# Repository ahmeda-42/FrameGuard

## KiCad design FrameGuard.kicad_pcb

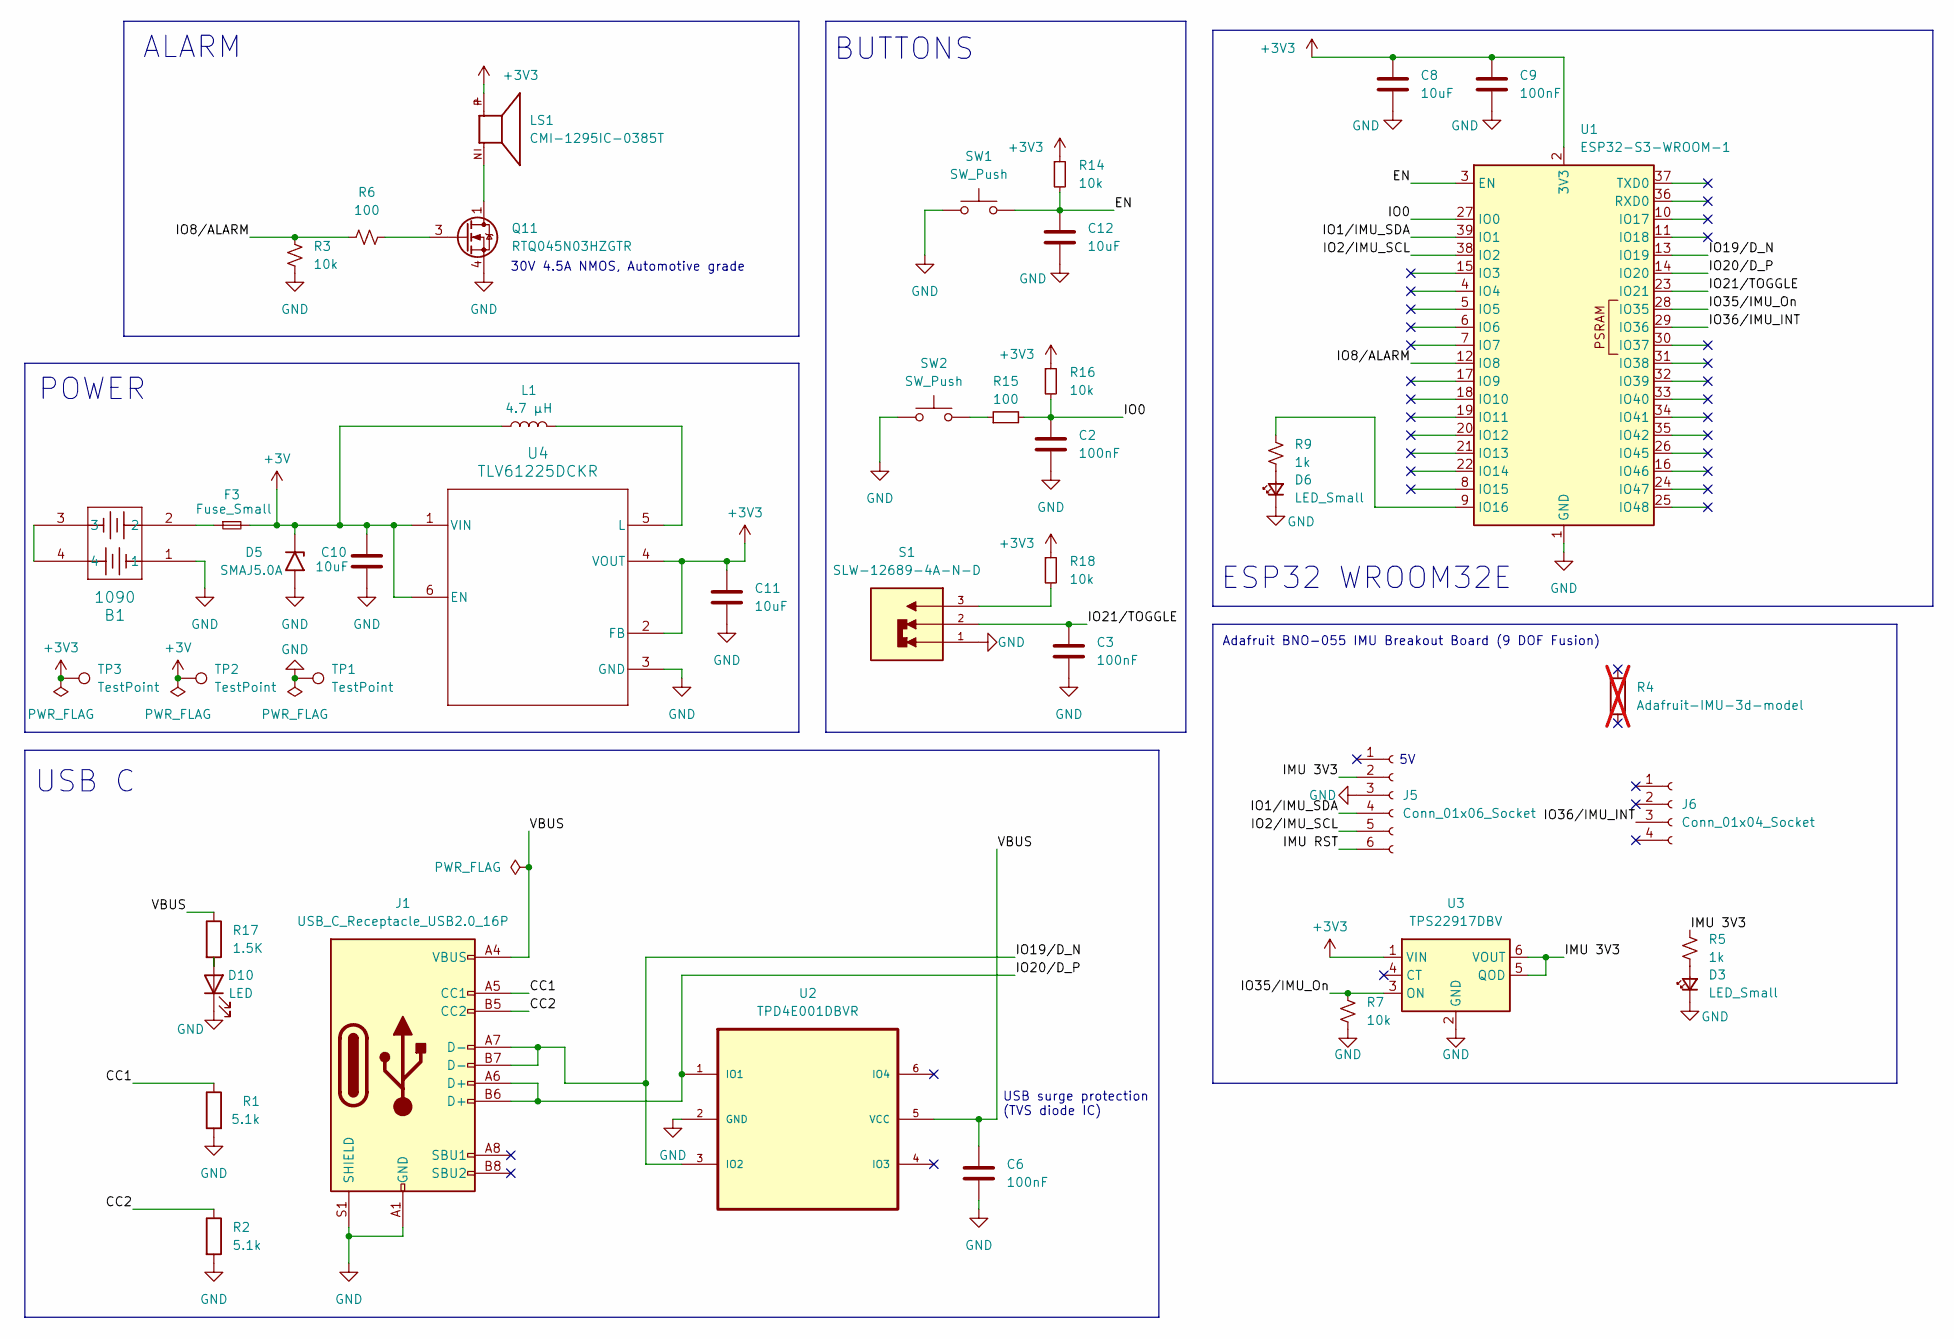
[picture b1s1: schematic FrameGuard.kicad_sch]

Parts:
B1: 1090; BATTERY-1090_KEY
C2, C3, C6, C9: 100nF; C_0603_1608Metric_Pad1.08x0.95mm_HandSolder
C8, C10, C11, C12: 10uF; C_0603_1608Metric_Pad1.08x0.95mm_HandSolder
D3, D6: LED_Small; LED_0805_2012Metric_Pad1.15x1.40mm_HandSolder
D5: SMAJ5.0A; D_SMA_Handsoldering
D10: LED; LED_0603_1608Metric_Pad1.05x0.95mm_HandSolder
F3: Fuse_Small; Fuse_1812_4532Metric_Pad1.30x3.40mm_HandSolder
J1: USB_C_Receptacle_USB2.0_16P; USB_C_Receptacle_GCT_USB4085
J5: Conn_01x06_Socket; PinSocket_1x06_P2.54mm_Vertical
J6: Conn_01x04_Socket; PinSocket_1x04_P2.54mm_Vertical
L1: 4.7 µH; L_0805_2012Metric_Pad1.05x1.20mm_HandSolder
LS1: CMI-1295IC-0385T; BUZZER-CUI_CMI-1295IC-0385T; PARTREV 1.0
Q11: RTQ045N03HZGTR; TSOT-23-6_HandSoldering
R1, R2: 5.1k; R_0603_1608Metric_Pad0.98x0.95mm_HandSolder
R3: 10k; R_0603_1608Metric_Pad0.98x0.95mm_HandSolder
R4: Adafruit-IMU-3d-model; R_0603_1608Metric_Pad0.98x0.95mm_HandSolder; not fitted
R5, R9: 1k; R_0805_2012Metric_Pad1.20x1.40mm_HandSolder
R6: 100; R_0603_1608Metric_Pad0.98x0.95mm_HandSolder
R7: 10k; R_0805_2012Metric_Pad1.20x1.40mm_HandSolder
R14, R16, R18: 10k; C_0603_1608Metric_Pad1.08x0.95mm_HandSolder
R15: 100; C_0603_1608Metric_Pad1.08x0.95mm_HandSolder
R17: 1.5K; R_0603_1608Metric_Pad0.98x0.95mm_HandSolder
S1: SLW-12689-4A-N-D; SWITCH-SW_SLW-12689-4A-N-D; PARTREV 1.01
SW1, SW2: SW_Push; SW_Tactile_SPST_NO_Straight_CK_PTS636Sx25SMTRLFS
TP1, TP2, TP3: TestPoint; TestPoint_Keystone_5000-5004_Miniature
U1: ESP32-S3-WROOM-1
U2: TPD4E001DBVR; SOT-23-6
U3: TPS22917DBV; SOT-23-6
U4: TLV61225DCKR; SOT-363_SC-70-6

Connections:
+3V: C10.1, D5.1 (A1), F3.2, L1.1, TP2.1, U4.1 (VIN), U4.6 (EN); also elsewhere on the board
+3V3: C8.1, C9.1, C11.1, LS1.P, R14.1, R16.1, R18.1, TP3.1, U1.2 (3V3), U3.1 (VIN), U4.2 (FB), U4.4 (VOUT); also elsewhere on the board
/CC1: J1.A5 (CC1), R1.1
/CC2: J1.B5 (CC2), R2.1
/EN: C12.1, R14.2, SW1.2, U1.3 (EN)
/IMU 3V3: J5.2, R5.1, U3.5 (QOD), U3.6 (VOUT)
/IMU RST: J5.6
/IO0: C2.1, R15.2, R16.2, U1.27 (IO0)
/IO1/IMU_SDA: J5.4, U1.39 (IO1)
/IO2/IMU_SCL: J5.5, U1.38 (IO2)
/IO8/ALARM: R3.1, R6.1, U1.12 (IO8)
/IO19/D_N: J1.A7 (D-), J1.B7 (D-), U1.13 (IO19), U2.3 (IO2)
/IO20/D_P: J1.A6 (D+), J1.B6 (D+), U1.14 (IO20), U2.1 (IO1)
/IO21/TOGGLE: C3.1, S1.2, U1.23 (IO21)
/IO35/IMU_On: R7.1, U1.28 (IO35), U3.3 (ON)
/IO36/IMU_INT: J6.3 (Pin_3_3), U1.29 (IO36)
/VBUS: C6.1, J1.A4 (VBUS), J1.A9 (VBUS), J1.B4 (VBUS), J1.B9 (VBUS), R17.1, U2.5 (VCC)
GND: B1.1, C2.2, C3.2, C6.2, C8.2, C9.2, C10.2, C11.2, C12.2, D3.1 (K), D5.2 (A2), D6.1 (K), D10.1 (K), J1.A1 (GND), J1.A12 (GND), J1.B1 (GND), J1.B12 (GND), J1.S1 (SHIELD), J5.3, Q11.4 (S), R1.2, R2.2, R3.2, R7.2, S1.1, SW1.1, SW2.1, TP1.1, U1.1 (GND), U1.40 (GND), U1.41 (GND), U2.2 (GND), U3.2 (GND), U4.3 (GND); also elsewhere on the board
unnamed: B1.2, F3.1
unnamed: B1.3, B1.4
unnamed: D3.2 (A), R5.2
unnamed: D6.2 (A), R9.2
unnamed: D10.2 (A), R17.2
unnamed: LS1.N, Q11.1 (D), Q11.2 (D), Q11.5 (D), Q11.6 (D)
unnamed: Q11.3 (G), R6.2
unnamed: R15.1, SW2.2
unnamed: R18.2, S1.3
unnamed: R9.1, U1.9 (IO16)
unnamed: L1.2, U4.5 (L)

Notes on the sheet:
USB surge protection (TVS diode IC)
USB C
30V 4.5A NMOS, Automotive grade
ALARM
BUTTONS
POWER
Adafruit BNO-055 IMU Breakout Board (9 DOF Fusion)
ESP32 WROOM32E

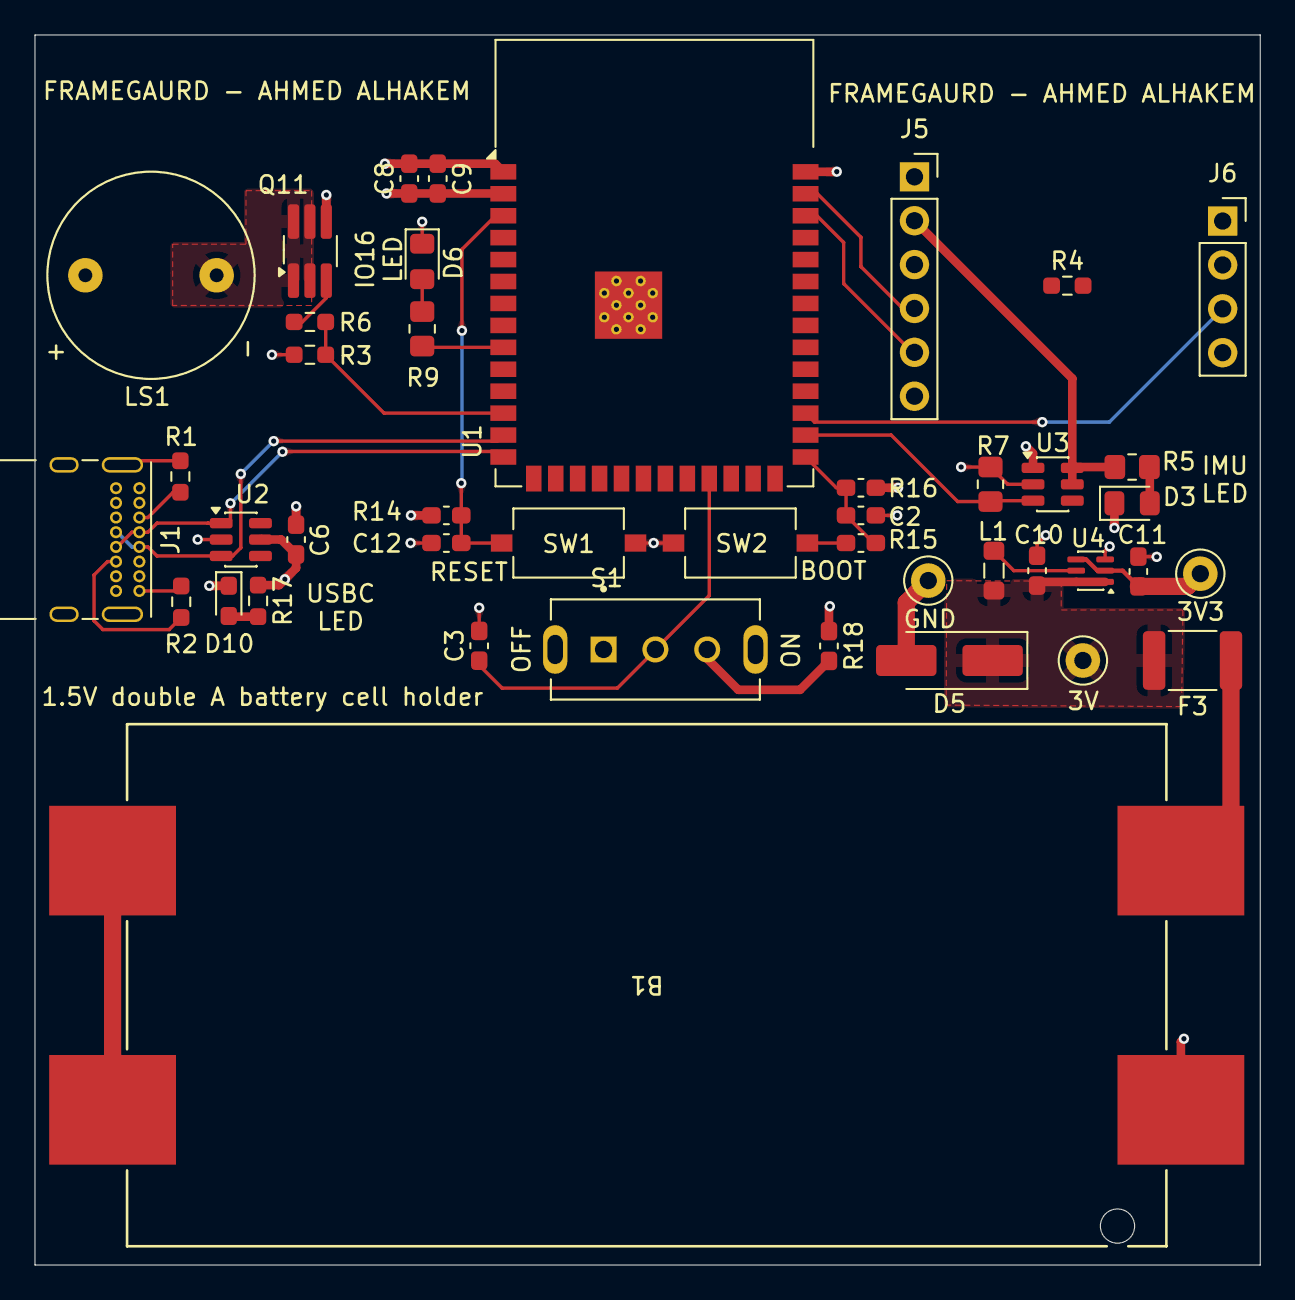
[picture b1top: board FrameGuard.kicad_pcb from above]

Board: 4 copper layers, 70.9 x 71.2 mm, 43 parts (0 on the bottom side), 28 nets.

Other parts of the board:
3V, 3V3: TestPoint; TestPoint_Keystone_5000-5004_Miniature
GND: TestPoint; TestPoint_Keystone_5000-5004_Miniature

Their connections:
+3V: 3V.1 (1_1); also elsewhere on the board
+3V3: 3V3.1 (1_1); also elsewhere on the board
GND: GND.1 (1_1); also elsewhere on the board

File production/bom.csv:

Designator,Footprint,Quantity,Value,LCSC Part #
"3V, 3V3, GND",TestPoint_Keystone_5000-5004_Miniature,3,TestPoint,
B1,BATTERY-1090_KEY,1,1090,
"C10, C11, C12, C8",0603,4,10uF,
"C2, C3, C6, C9",0603,4,100nF,
D10,0603,1,LED,
"D3, D6",0805,2,LED_Small,
D5,D_SMA_Handsoldering,1,SMAJ5.0A,
F3,1812,1,Fuse_Small,
J1,USB_C_Receptacle_GCT_USB4085,1,USB_C_Receptacle_USB2.0_16P,
J5,PinSocket_1x06_P2.54mm_Vertical,1,Conn_01x06_Socket,
J6,PinSocket_1x04_P2.54mm_Vertical,1,Conn_01x04_Socket,
L1,0805,1,4.7 µH,
LS1,BUZZER-CUI_CMI-1295IC-0385T,1,CMI-1295IC-0385T,
Q11,TSOT-23-6_HandSoldering,1,RTQ045N03HZGTR,
"R1, R2",0603,2,5.1k,
"R14, R16, R18, R3",0603,4,10k,
"R15, R6",0603,2,100,
R17,0603,1,1.5K,
"R5, R9",0805,2,1k,
R7,0805,1,10k,
S1,SWITCH-SW_SLW-12689-4A-N-D,1,SLW-12689-4A-N-D,
"SW1, SW2",SW_Tactile_SPST_NO_Straight_CK_PTS636Sx25SMTRLFS,2,SW_Push,
U1,ESP32-S3-WROOM-1,1,ESP32-S3-WROOM-1,
U2,SOT-23-6,1,TPD4E001DBVR,
U3,SOT-23-6,1,TPS22917DBV,
U4,SOT-363_SC-70-6,1,TLV61225DCKR,
